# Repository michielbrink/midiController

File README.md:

# midiController
a big midi controller with 64 potmeters and 16 buttons

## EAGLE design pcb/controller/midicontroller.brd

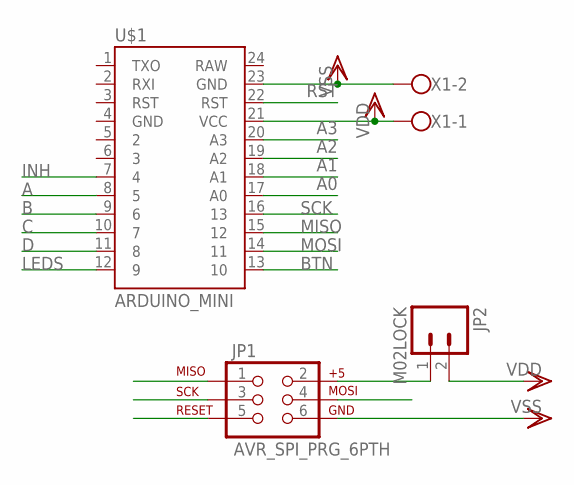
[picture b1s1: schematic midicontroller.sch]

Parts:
JP1: AVR_SPI_PRG_6PTH; 2X3
JP2: M02LOCK; 1X02_LOCK
U$1: ARDUINO_MINI
X1: W237-102

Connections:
A: U$1.8 (5)
A0: U$1.17 (A0)
A1: U$1.18 (A1)
A2: U$1.19 (A2)
A3: U$1.20 (A3)
B: U$1.9 (6)
BTN: U$1.13 (10)
C: U$1.10 (7)
D: U$1.11 (8)
INH: U$1.7 (4)
LEDS: U$1.12 (9)
MISO: JP1.1, U$1.15 (12)
MOSI: JP1.4, U$1.14 (11)
unnamed: JP1.2, JP2.1
RST: JP1.5, U$1.22 (RST)
SCK: JP1.3, U$1.16 (13)
VDD: JP2.2, U$1.21 (VCC), X1.1
VSS: JP1.6, U$1.23 (GND), X1.2

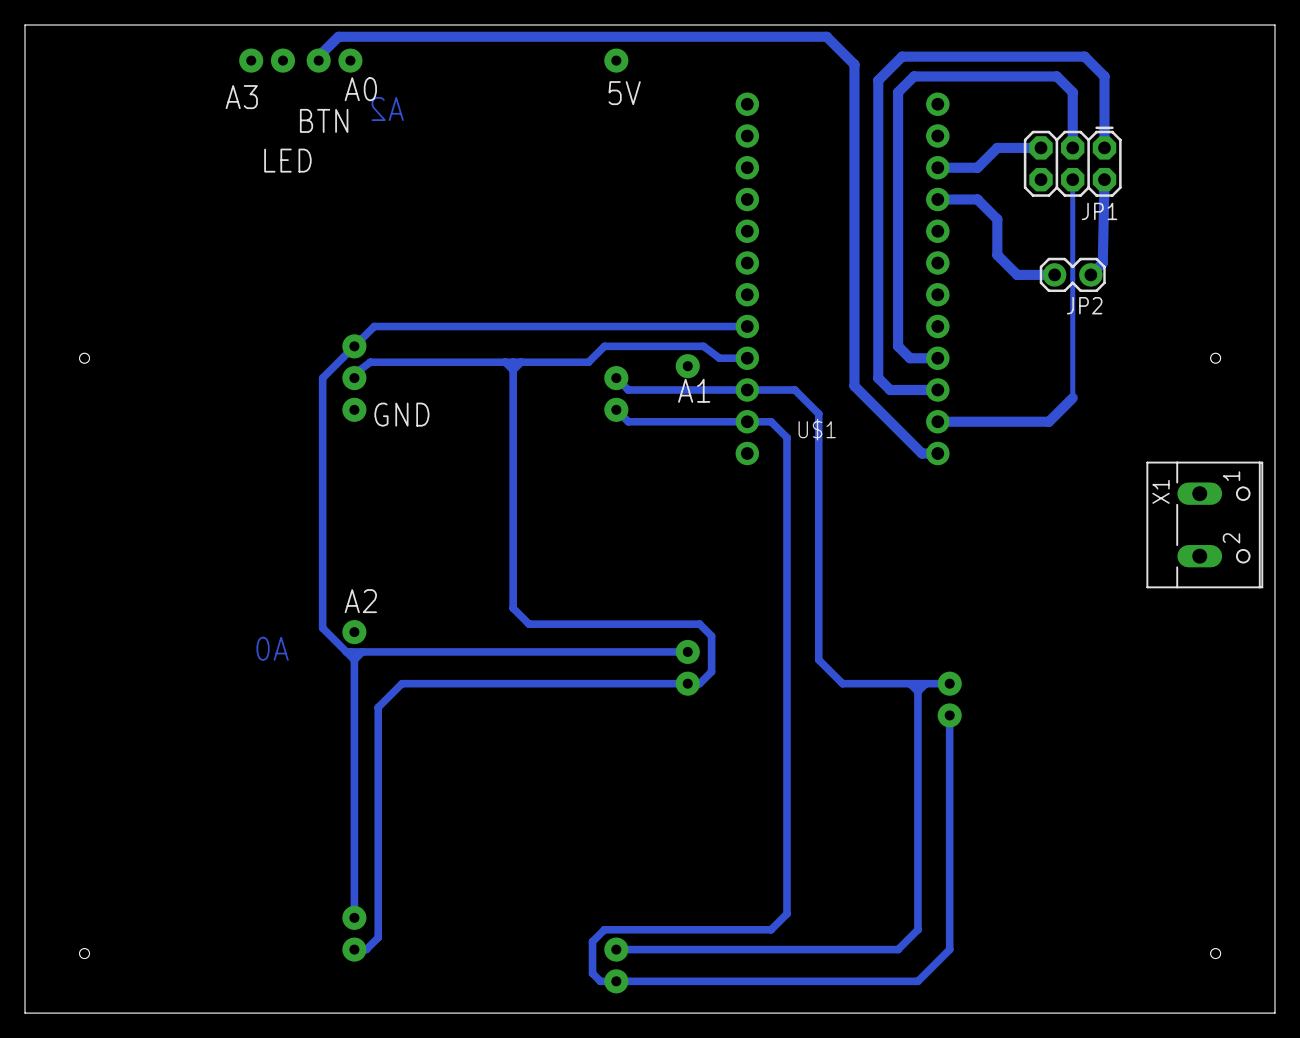
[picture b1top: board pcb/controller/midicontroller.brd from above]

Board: 2 copper layers, 100.0 x 79.0 mm, 4 parts (0 on the bottom side), 7 nets.

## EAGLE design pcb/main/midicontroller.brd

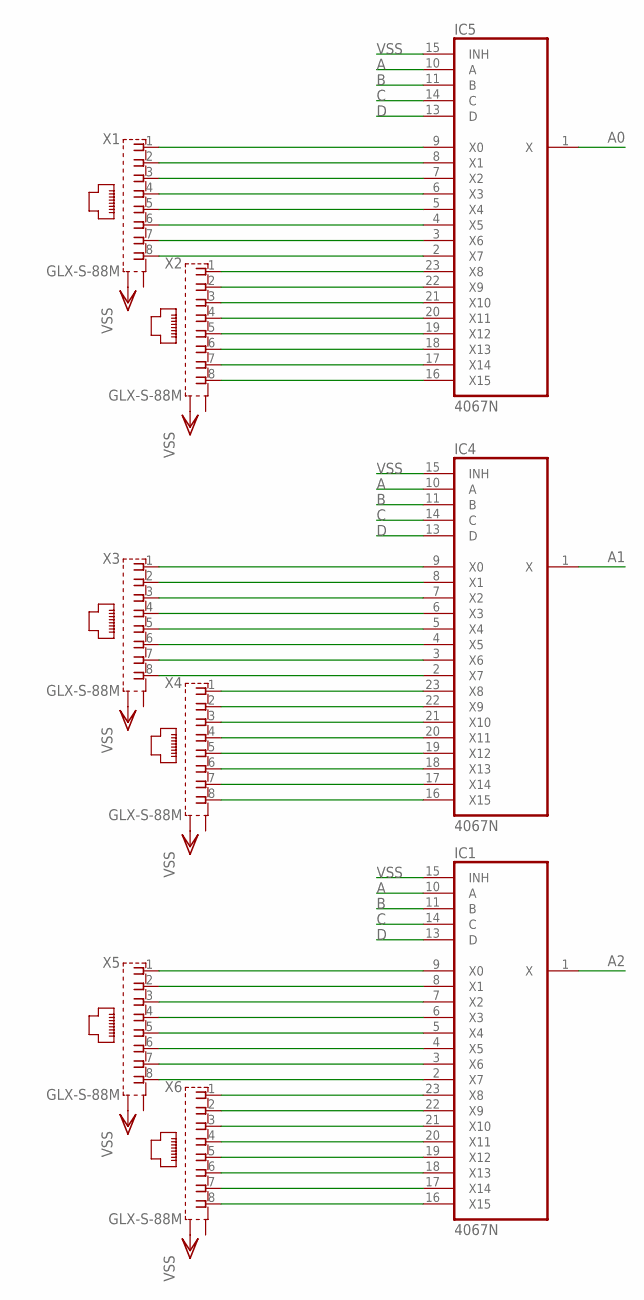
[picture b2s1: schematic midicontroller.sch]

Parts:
IC1, IC4, IC5: 4067N; DIL24-6
X1, X2, X3, X4, X5, X6: GLX-S-88M

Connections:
A: IC1.10 (A), IC4.10 (A), IC5.10 (A)
A0: IC5.1 (X)
A1: IC4.1 (X)
A2: IC1.1 (X)
B: IC1.11 (B), IC4.11 (B), IC5.11 (B)
C: IC1.14 (C), IC4.14 (C), IC5.14 (C)
D: IC1.13 (D), IC4.13 (D), IC5.13 (D)
unnamed: IC5.8 (X1), X1.2
unnamed: IC5.7 (X2), X1.3
unnamed: IC5.6 (X3), X1.4
unnamed: IC5.5 (X4), X1.5
unnamed: IC5.4 (X5), X1.6
unnamed: IC5.3 (X6), X1.7
unnamed: IC5.2 (X7), X1.8
unnamed: IC5.23 (X8), X2.1
unnamed: IC5.22 (X9), X2.2
unnamed: IC5.21 (X10), X2.3
unnamed: IC5.20 (X11), X2.4
unnamed: IC5.19 (X12), X2.5
unnamed: IC5.18 (X13), X2.6
unnamed: IC5.17 (X14), X2.7
unnamed: IC5.16 (X15), X2.8
unnamed: IC4.9 (X0), X3.1
unnamed: IC4.8 (X1), X3.2
unnamed: IC4.7 (X2), X3.3
unnamed: IC4.6 (X3), X3.4
unnamed: IC4.5 (X4), X3.5
unnamed: IC4.4 (X5), X3.6
unnamed: IC4.3 (X6), X3.7
unnamed: IC4.2 (X7), X3.8
unnamed: IC4.23 (X8), X4.1
unnamed: IC4.22 (X9), X4.2
unnamed: IC4.21 (X10), X4.3
unnamed: IC4.20 (X11), X4.4
unnamed: IC4.19 (X12), X4.5
unnamed: IC4.18 (X13), X4.6
unnamed: IC4.17 (X14), X4.7
unnamed: IC4.16 (X15), X4.8
unnamed: IC1.9 (X0), X5.1
unnamed: IC1.8 (X1), X5.2
unnamed: IC1.7 (X2), X5.3
unnamed: IC1.6 (X3), X5.4
unnamed: IC1.5 (X4), X5.5
unnamed: IC1.4 (X5), X5.6
unnamed: IC1.3 (X6), X5.7
unnamed: IC1.2 (X7), X5.8
unnamed: IC1.23 (X8), X6.1
unnamed: IC1.22 (X9), X6.2
unnamed: IC1.21 (X10), X6.3
unnamed: IC1.20 (X11), X6.4
unnamed: IC1.19 (X12), X6.5
unnamed: IC1.18 (X13), X6.6
unnamed: IC1.17 (X14), X6.7
unnamed: IC1.16 (X15), X6.8
unnamed: IC5.9 (X0), X1.1
VDD: IC1.24 (VDD), IC4.24 (VDD), IC5.24 (VDD)
VSS: IC1.12 (VSS), IC1.15 (INH), IC4.12 (VSS), IC4.15 (INH), IC5.12 (VSS), IC5.15 (INH), X1.S2, X2.S2, X3.S2, X4.S2, X5.S2, X6.S2

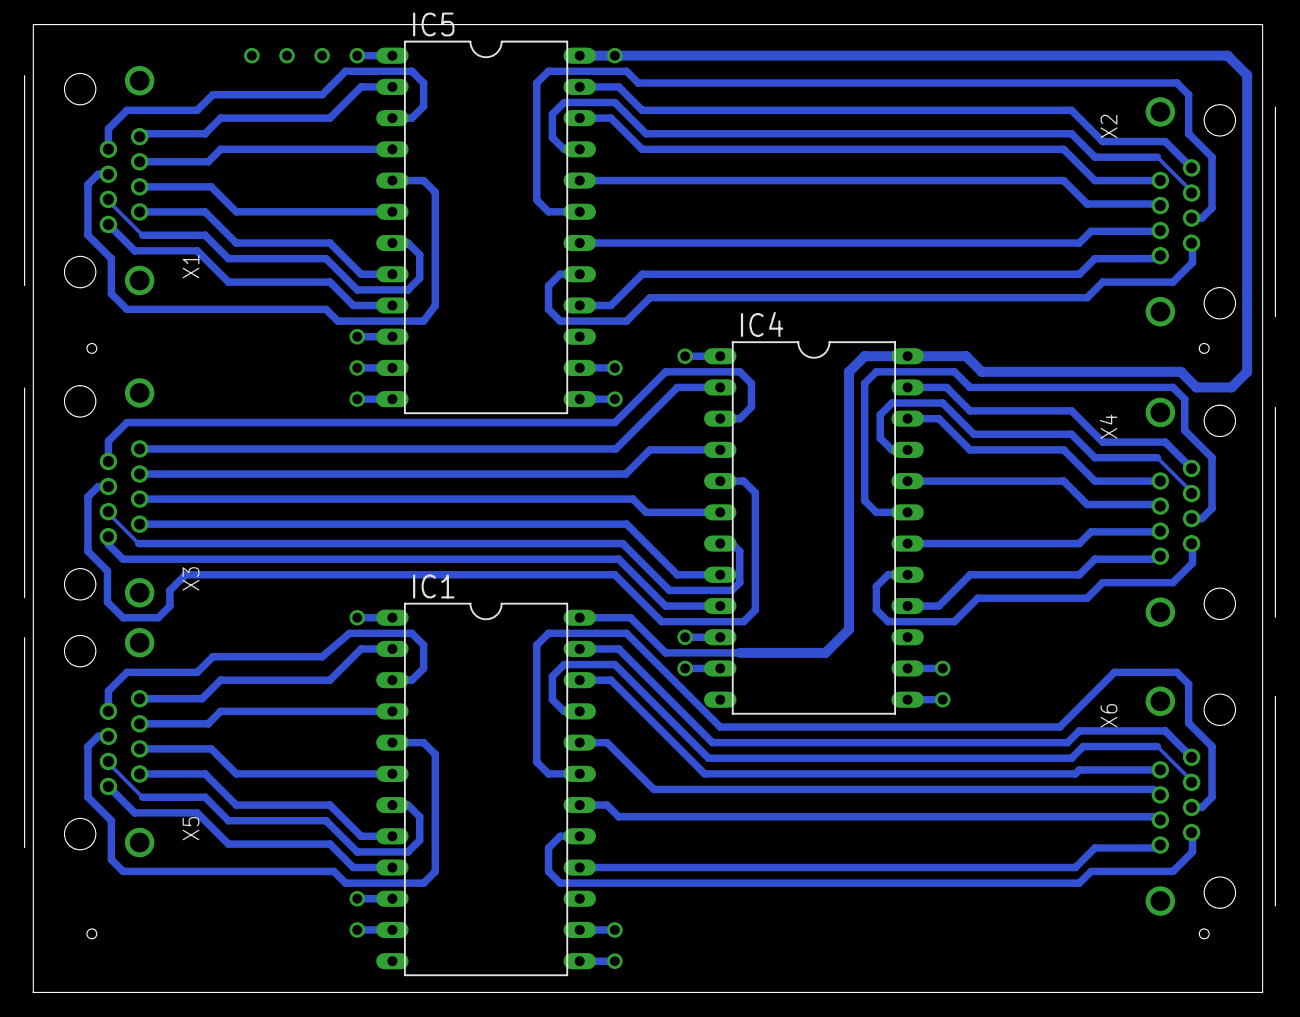
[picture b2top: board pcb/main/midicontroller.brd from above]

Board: 2 copper layers, 101.8 x 78.7 mm, 9 parts (0 on the bottom side), 54 nets.

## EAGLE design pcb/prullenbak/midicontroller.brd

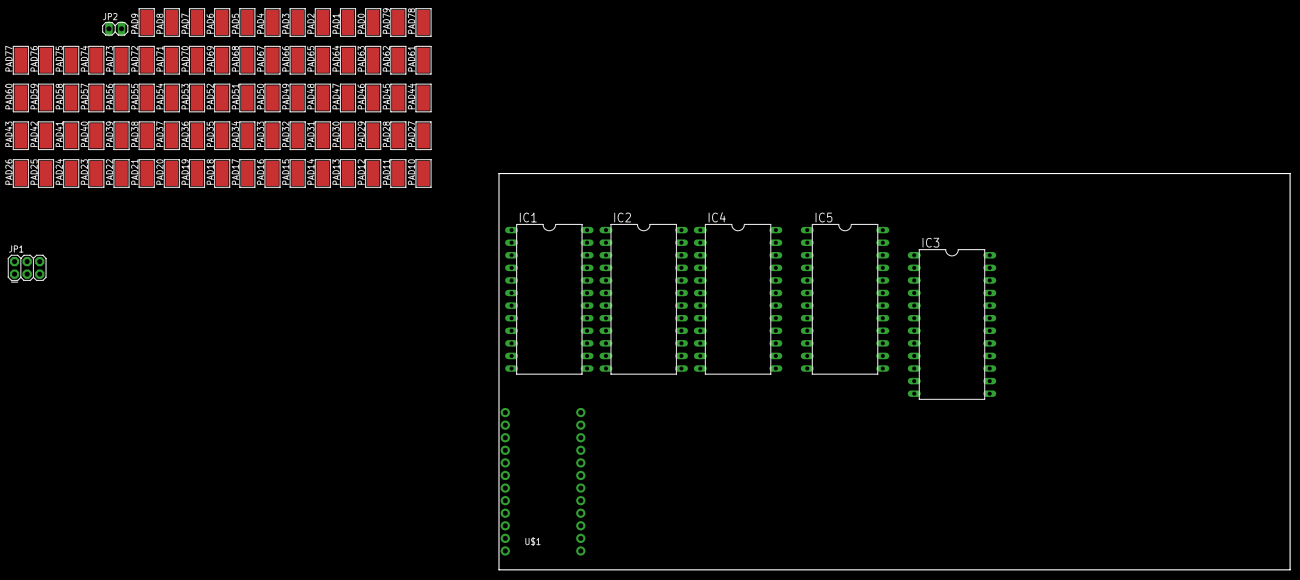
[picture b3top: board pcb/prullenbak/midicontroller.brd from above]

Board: 2 copper layers, 159.7 x 80.0 mm, 88 parts (0 on the bottom side), 98 nets, no tracks yet.

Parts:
IC1, IC2, IC3, IC4, IC5: 4067N; DIL24-6
JP1: AVR_SPI_PRG_6PTH; 2X3
JP2: 1X02
PAD0, PAD1, PAD2, PAD3, PAD4, PAD5, PAD6, PAD7, PAD8, PAD9, PAD10, PAD11, PAD12, PAD13, PAD14, PAD15, PAD16, PAD17, PAD18, PAD19, PAD20, PAD21, PAD22, PAD23, PAD24, PAD25, PAD26, PAD27, PAD28, PAD29, PAD30, PAD31, PAD32, PAD33, PAD34, PAD35, PAD36, PAD37, PAD38, PAD39, PAD40, PAD41, PAD42, PAD43, PAD44, PAD45, PAD46, PAD47, PAD48, PAD49, PAD50, PAD51, PAD52, PAD53, PAD54, PAD55, PAD56, PAD57, PAD58, PAD59, PAD60, PAD61, PAD62, PAD63, PAD64, PAD65, PAD66, PAD67, PAD68, PAD69, PAD70, PAD71, PAD72, PAD73, PAD74, PAD75, PAD76, PAD77, PAD78, PAD79: WIREPADSMD5-2,5; 5-2,5
U$1: ARDUINO_PRO_MICRO

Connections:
A: IC1.10, IC2.10, IC3.10, IC4.10, IC5.10
A0: IC5.1, U$1.17
A1: IC4.1, U$1.18
A2: IC3.1, U$1.19
A3: IC2.1, U$1.20
B: IC1.11, IC2.11, IC3.11, IC4.11, IC5.11
C: IC1.14, IC2.14, IC3.14, IC4.14, IC5.14
D: IC1.13, IC2.13, IC3.13, IC4.13, IC5.13
D10: IC1.1, U$1.13
GND: JP1.6, U$1.23
INH: IC1.15, IC2.15, IC3.15, IC4.15, IC5.15
MISO: JP1.1, U$1.15
MOSI: JP1.4, U$1.14
unnamed: IC5.8, PAD1.1
unnamed: IC5.7, PAD2.1
unnamed: IC5.6, PAD3.1
unnamed: IC5.5, PAD4.1
unnamed: IC5.4, PAD5.1
unnamed: IC5.3, PAD6.1
unnamed: IC5.2, PAD7.1
unnamed: IC5.23, PAD8.1
unnamed: IC5.22, PAD9.1
unnamed: IC5.21, PAD10.1
unnamed: IC5.20, PAD11.1
unnamed: IC5.19, PAD12.1
unnamed: IC5.18, PAD13.1
unnamed: IC5.17, PAD14.1
unnamed: IC5.16, PAD15.1
unnamed: IC4.9, PAD16.1
unnamed: IC4.8, PAD17.1
unnamed: IC4.7, PAD18.1
unnamed: IC4.6, PAD19.1
unnamed: IC4.5, PAD20.1
unnamed: IC4.4, PAD21.1
unnamed: IC4.3, PAD22.1
unnamed: IC4.2, PAD23.1
unnamed: IC4.23, PAD24.1
unnamed: IC4.22, PAD25.1
unnamed: IC4.21, PAD26.1
unnamed: IC4.20, PAD27.1
unnamed: IC4.19, PAD28.1
unnamed: IC4.18, PAD29.1
unnamed: IC4.17, PAD30.1
unnamed: IC4.16, PAD31.1
unnamed: IC3.9, PAD32.1
unnamed: IC3.8, PAD33.1
unnamed: IC3.7, PAD34.1
unnamed: IC3.6, PAD35.1
unnamed: IC3.5, PAD36.1
unnamed: IC3.4, PAD37.1
unnamed: IC3.3, PAD38.1
unnamed: IC3.2, PAD39.1
unnamed: IC3.23, PAD40.1
unnamed: IC3.22, PAD41.1
unnamed: IC3.21, PAD42.1
unnamed: IC3.20, PAD43.1
unnamed: IC3.18, PAD45.1
unnamed: IC3.17, PAD46.1
unnamed: IC3.16, PAD47.1
unnamed: IC2.9, PAD48.1
unnamed: IC2.8, PAD49.1
unnamed: IC2.7, PAD50.1
unnamed: IC2.6, PAD51.1
unnamed: IC2.5, PAD52.1
unnamed: IC2.4, PAD53.1
unnamed: IC2.3, PAD54.1
unnamed: IC2.2, PAD55.1
unnamed: IC2.23, PAD56.1
unnamed: IC2.22, PAD57.1
unnamed: IC2.21, PAD58.1
unnamed: IC2.20, PAD59.1
unnamed: IC2.19, PAD60.1
unnamed: IC2.18, PAD61.1
unnamed: IC2.17, PAD62.1
unnamed: IC2.16, PAD63.1
unnamed: IC1.9, PAD64.1
unnamed: IC1.8, PAD65.1
unnamed: IC1.7, PAD66.1
unnamed: IC1.6, PAD67.1
unnamed: IC1.5, PAD68.1
unnamed: IC1.4, PAD69.1
unnamed: IC1.3, PAD70.1
unnamed: IC1.2, PAD71.1
unnamed: IC1.23, PAD72.1
unnamed: IC1.22, PAD73.1
unnamed: IC1.21, PAD74.1
unnamed: IC1.20, PAD75.1
unnamed: IC1.19, PAD76.1
unnamed: IC1.18, PAD77.1
unnamed: IC1.17, PAD78.1
unnamed: IC1.16, PAD79.1
unnamed: IC5.9, PAD0.1
unnamed: JP1.2, JP2.1
RST: JP1.5, U$1.22
SCK: JP1.3, U$1.16
VCC: JP2.2, U$1.21
VDD: IC1.24, IC2.24, IC3.24, IC4.24, IC5.24
VSS: IC1.12, IC2.12, IC3.12, IC4.12, IC5.12

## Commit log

2015-04-18 add files to git
2015-04-18 add pictures
2015-04-18 add pin numbers to the pins
2015-04-22 add arrays in code and add code to get the leds working ;)
2015-04-28 fix some bugs
2015-05-01 add buttons

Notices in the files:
parts and their libraries:
SparkFun-Boards: Licensing: Creative Commons ShareAlike 4.0 International - https://creativecommons.org/licenses/by-sa/4.0
